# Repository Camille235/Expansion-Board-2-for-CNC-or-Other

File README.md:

# Expansion Board 2 - CNC/Other
Expansion Board to Arduino CNC

Hi!

The repository contains a miniproject with an Open Source Expansion Board.

This Expansion Board , named "ExpBoard 2" is dedicated for an Arduino Uno CNC (or similar project).

ExpBoard 2 have:

  # INPUTS
  10 inputs with a connector 5x2.
  
    1: Vcc 5V
    2: GND  
    3: SCL
    4: SDA
    5: RESET/ABORT
    6: FEED/HOLD
    7: GND
    8: CYCLE/START
    9: Vcc 12V
    10: GND
  # OUTPUTS
  6 outputs with two connectors.  
  
   FAN (or LED) connector (2 pins):
   
    1: Vcc 12V
    2: GND
    
   LCD I2C. For 16x2, 20x2 or 20x4 LCD. Header connector (4 pins):

    1: SCL
    2: SDA
    3: Vcc 5V
    4: GND
   # PUSH-BOTTONS 
    
    1: CYCLE/START
    2: RESET/ABORT
    3: FEED HOLD

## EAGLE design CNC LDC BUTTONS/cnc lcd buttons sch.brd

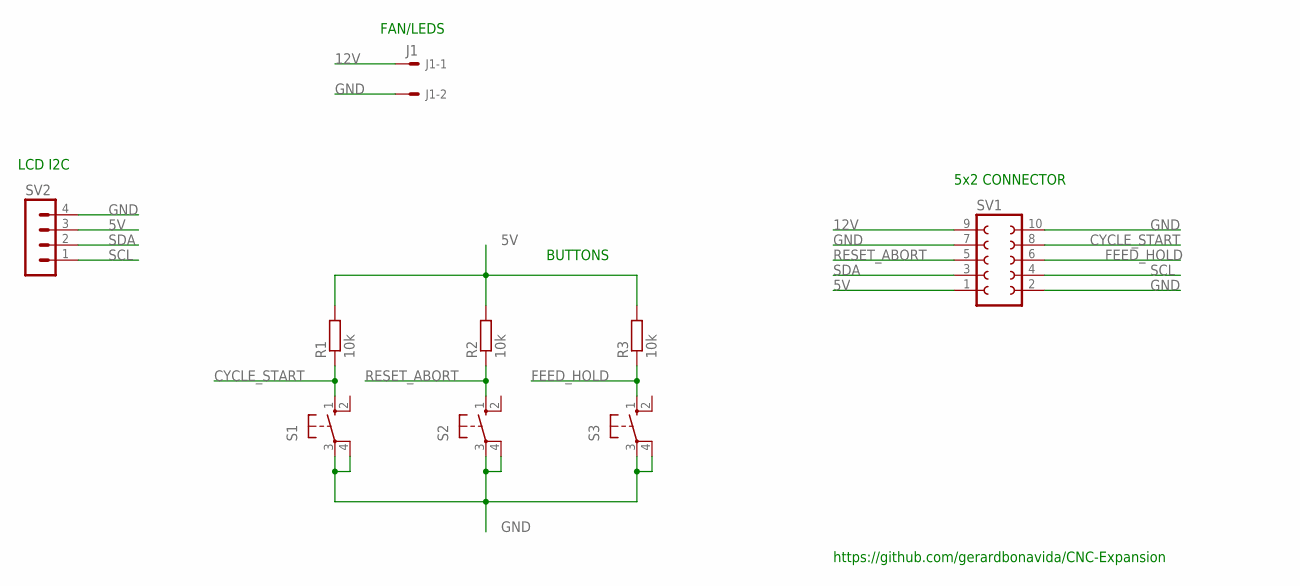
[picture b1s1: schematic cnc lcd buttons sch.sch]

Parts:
J1: J1; 6410-02
R1, R2, R3: 10k; 0309/12
S1, S2, S3: 10-XX; B3F-10XX
SV1: FE05-2
SV2: MA04-1

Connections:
5V: R1.2, R2.2, R3.2, SV1.1, SV2.3
12V: J1.1, SV1.9
CYCLE_START: R1.1, S1.1 (S), SV1.8
FEED_HOLD: R3.1, S3.1 (S), SV1.6
GND: J1.2, S1.3, S1.4 (P1), S2.3, S2.4 (P1), S3.3, S3.4 (P1), SV1.2, SV1.7, SV1.10, SV2.4
RESET_ABORT: R2.1, S2.1 (S), SV1.5
SCL: SV1.4, SV2.1
SDA: SV1.3, SV2.2

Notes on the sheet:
FAN/LEDS
5x2 CONNECTOR
BUTTONS
LCD I2C
https://github.com/gerardbonavida/CNC-Expansion

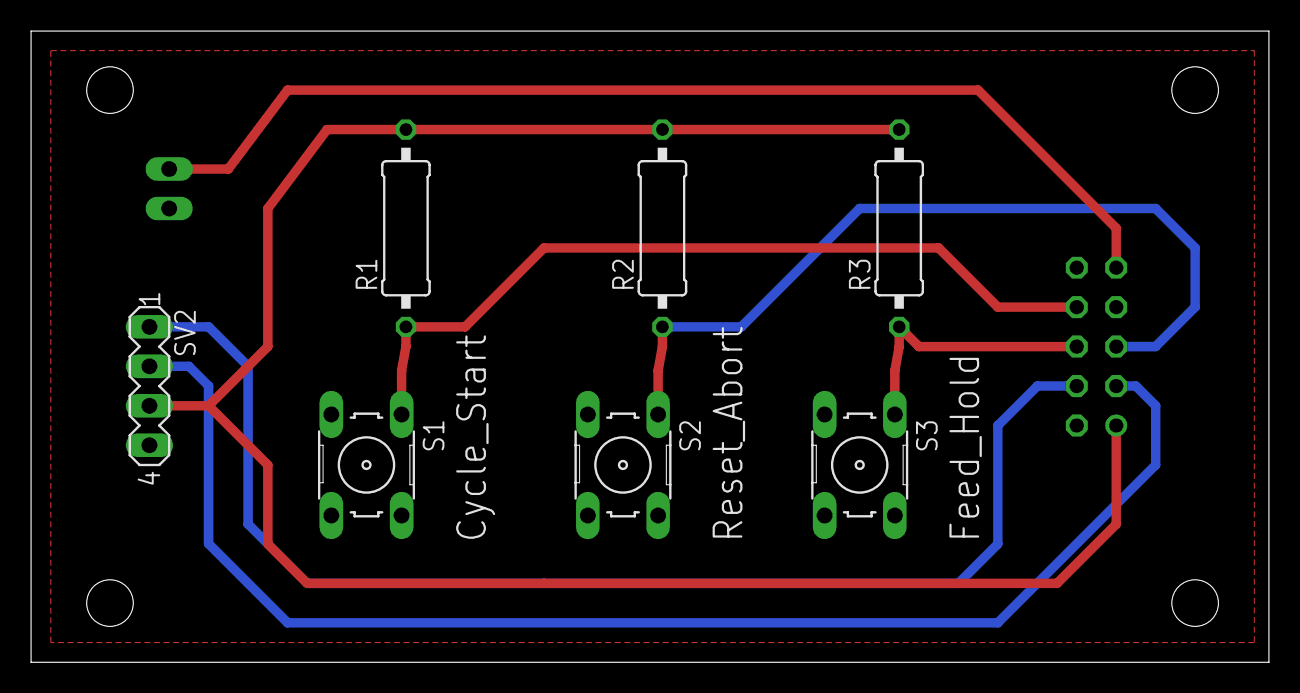
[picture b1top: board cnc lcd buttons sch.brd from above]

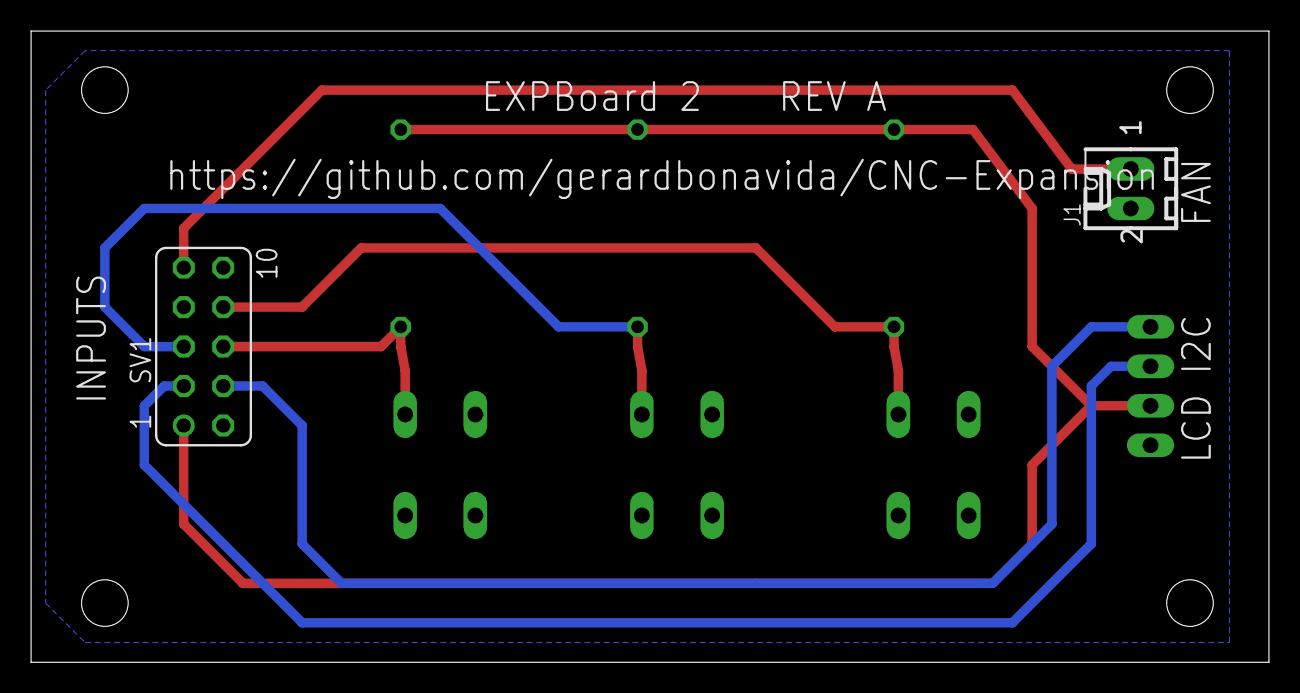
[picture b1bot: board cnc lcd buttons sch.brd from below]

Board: 2 copper layers, 79.7 x 40.6 mm, 9 parts (2 on the bottom side), 8 nets.
